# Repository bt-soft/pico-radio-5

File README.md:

# Pico-Radio-5

## Hardver részletesen

A Pico-Radio-5 egy fejlett, több sávos rádióvevő, amely a Raspberry Pi Pico (RP2040) mikrokontroller köré épül. A főbb hardverelemek:

- **Raspberry Pi Pico**  
  ARM Cortex-M0+ dual-core MCU, 2MB flash, 264kB RAM, USB programozás.
- **SI4735 rádió IC**  
  Digitális rádióvevő chip, amely támogatja az FM (RDS), AM (MW, LW, SW) sávokat, digitális vezérléssel (I2C).
- **TFT érintőkijelző**  
  320x240 vagy 480x320 felbontású, színes, érintésérzékeny kijelző (TFT_eSPI driverrel).
- **Rotary encoder**  
  Mechanikus forgó kódoló, amely a frekvencia, hangerő, menük vezérlésére szolgál (kattintás érzékelés is).
- **Hangkimenet**  
  3.5mm jack vagy beépített hangszóró, SI4735 audio kimenet közvetlenül vagy erősítőn keresztül.
- **Akkumulátor mérés**  
  Feszültségosztóval a Pico ADC-n keresztül, töltöttség kijelzés.
- **EEPROM**  
  Állomásmemória, beállítások tartós tárolása.
- **Egyéb**  
  Nyomógombok, szenzorok (pl. hőmérséklet), LED-ek, opcionális bővítések.

A részletes kapcsolási rajzok, NYÁK-tervek a `doc/` mappában találhatók:
- [Kapcsolási rajz (PDF)](doc/pico-radio-5-sch.pdf)
- [NYÁK terv (PDF)](doc/pico-radio-5-pcb.pdf)

## Szoftver részletesen

A szoftver PlatformIO környezetben, C++ nyelven, Arduino frameworkre épül. Főbb könyvtárak: PU2CLR SI4735, TFT_eSPI, RPI_PICO_TimerInterrupt.

### Fő funkciók

- **Rádió sávok**: FM (RDS), AM (MW, LW, SW), SSB/CW támogatás (ha SI4735 patch betöltve)
- **Állomáskeresés, finomhangolás**: automatikus és kézi keresés, lépésköz választás
- **Állomásmemória**: FM/AM/SW/LW sávonként, EEPROM-ban tárolva
- **RDS támogatás**: FM sávban állomásnév, rádiószöveg, PTY, óra
- **Grafikus kezelőfelület**: érintőképernyő, rotary encoder, menük, dialógusok, státuszsor
- **Képernyővédő**: animált frekvencia kijelzés, energiatakarékosság
- **Spektrumkijelzés**: FFT-alapú vizualizáció (ha támogatott)
- **Beállítások**: hangerő, sáv, lépésköz, kijelző fényerő, képernyővédő időzítés, stb.
- **Akkumulátor kijelzés**: töltöttség százalékban, színkódolva
- **Debug és diagnosztika**: soros porton részletes log, hibakereséshez

### Mappastruktúra

- `src/` – Fő forráskód (képernyők, rádió logika, UI, stb.)
- `include/` – Fejlécfájlok, interfészek, konstansok
- `doc/` – Dokumentáció, kapcsolási rajzok, NYÁK-tervek, minták
- `test/` – Egységtesztek, tesztkódok
- `platformio.ini` – PlatformIO projektkonfiguráció

### Főbb forrásfájlok

- `main.cpp` – Inicializálás, fő programciklus
- `ScreenFM.cpp`, `ScreenAM.cpp`, stb. – Különböző rádió sávok kezelői
- `ScreenSaverScreen.cpp` – Képernyővédő logika
- `FreqDisplay.cpp` – Frekvencia kijelző komponens
- `Config.cpp` – Beállítások kezelése, EEPROM mentés/betöltés
- `Si4735Manager.cpp` – SI4735 IC vezérlés, sávváltás, frekvenciaállítás

### Fordítás és feltöltés

1. Telepítsd a PlatformIO-t (ajánlott: VSCode bővítményként)
2. Nyisd meg a projektet VSCode-ban
3. Csatlakoztasd a Raspberry Pi Pico-t USB-n keresztül
4. Válaszd ki a Pico-t mint céleszközt
5. Kattints a Build (vagy Upload) gombra, vagy futtasd:  
   `pio run --target upload`
6. A feltöltés után a rádió automatikusan elindul

### Fejlesztői információk

- A kód moduláris, minden képernyő külön osztályban van
- A beállítások és állomásmemória EEPROM-ban tartósan tárolódik
- A hardveres I2C lábak, rotary encoder, kijelző, stb. pinjei a `pins.h`-ban konfigurálhatók
- Hibakereséshez a soros porton részletes log érhető el

## TFT_eSPI beállítás

A projekt a TFT_eSPI könyvtárat használja a kijelző kezeléséhez. A helyes működéshez a `doc/TFT_eSPI/User_Setup.h` fájlt be kell másolni a PlatformIO által használt TFT_eSPI könyvtár megfelelő mappájába. Ez általában:

```
.pio/libdeps/pico/TFT_eSPI/User_Setup.h
```

A másolás után a kijelző a projektben definiált beállításokkal fog működni. Ha másik kijelzőt használsz, módosítsd a `User_Setup.h`-t a saját hardveredhez.

## Licenc

A projekt szabadon felhasználható, módosítható, forrásmegjelöléssel. Lásd a forráskód fejléceit.

---

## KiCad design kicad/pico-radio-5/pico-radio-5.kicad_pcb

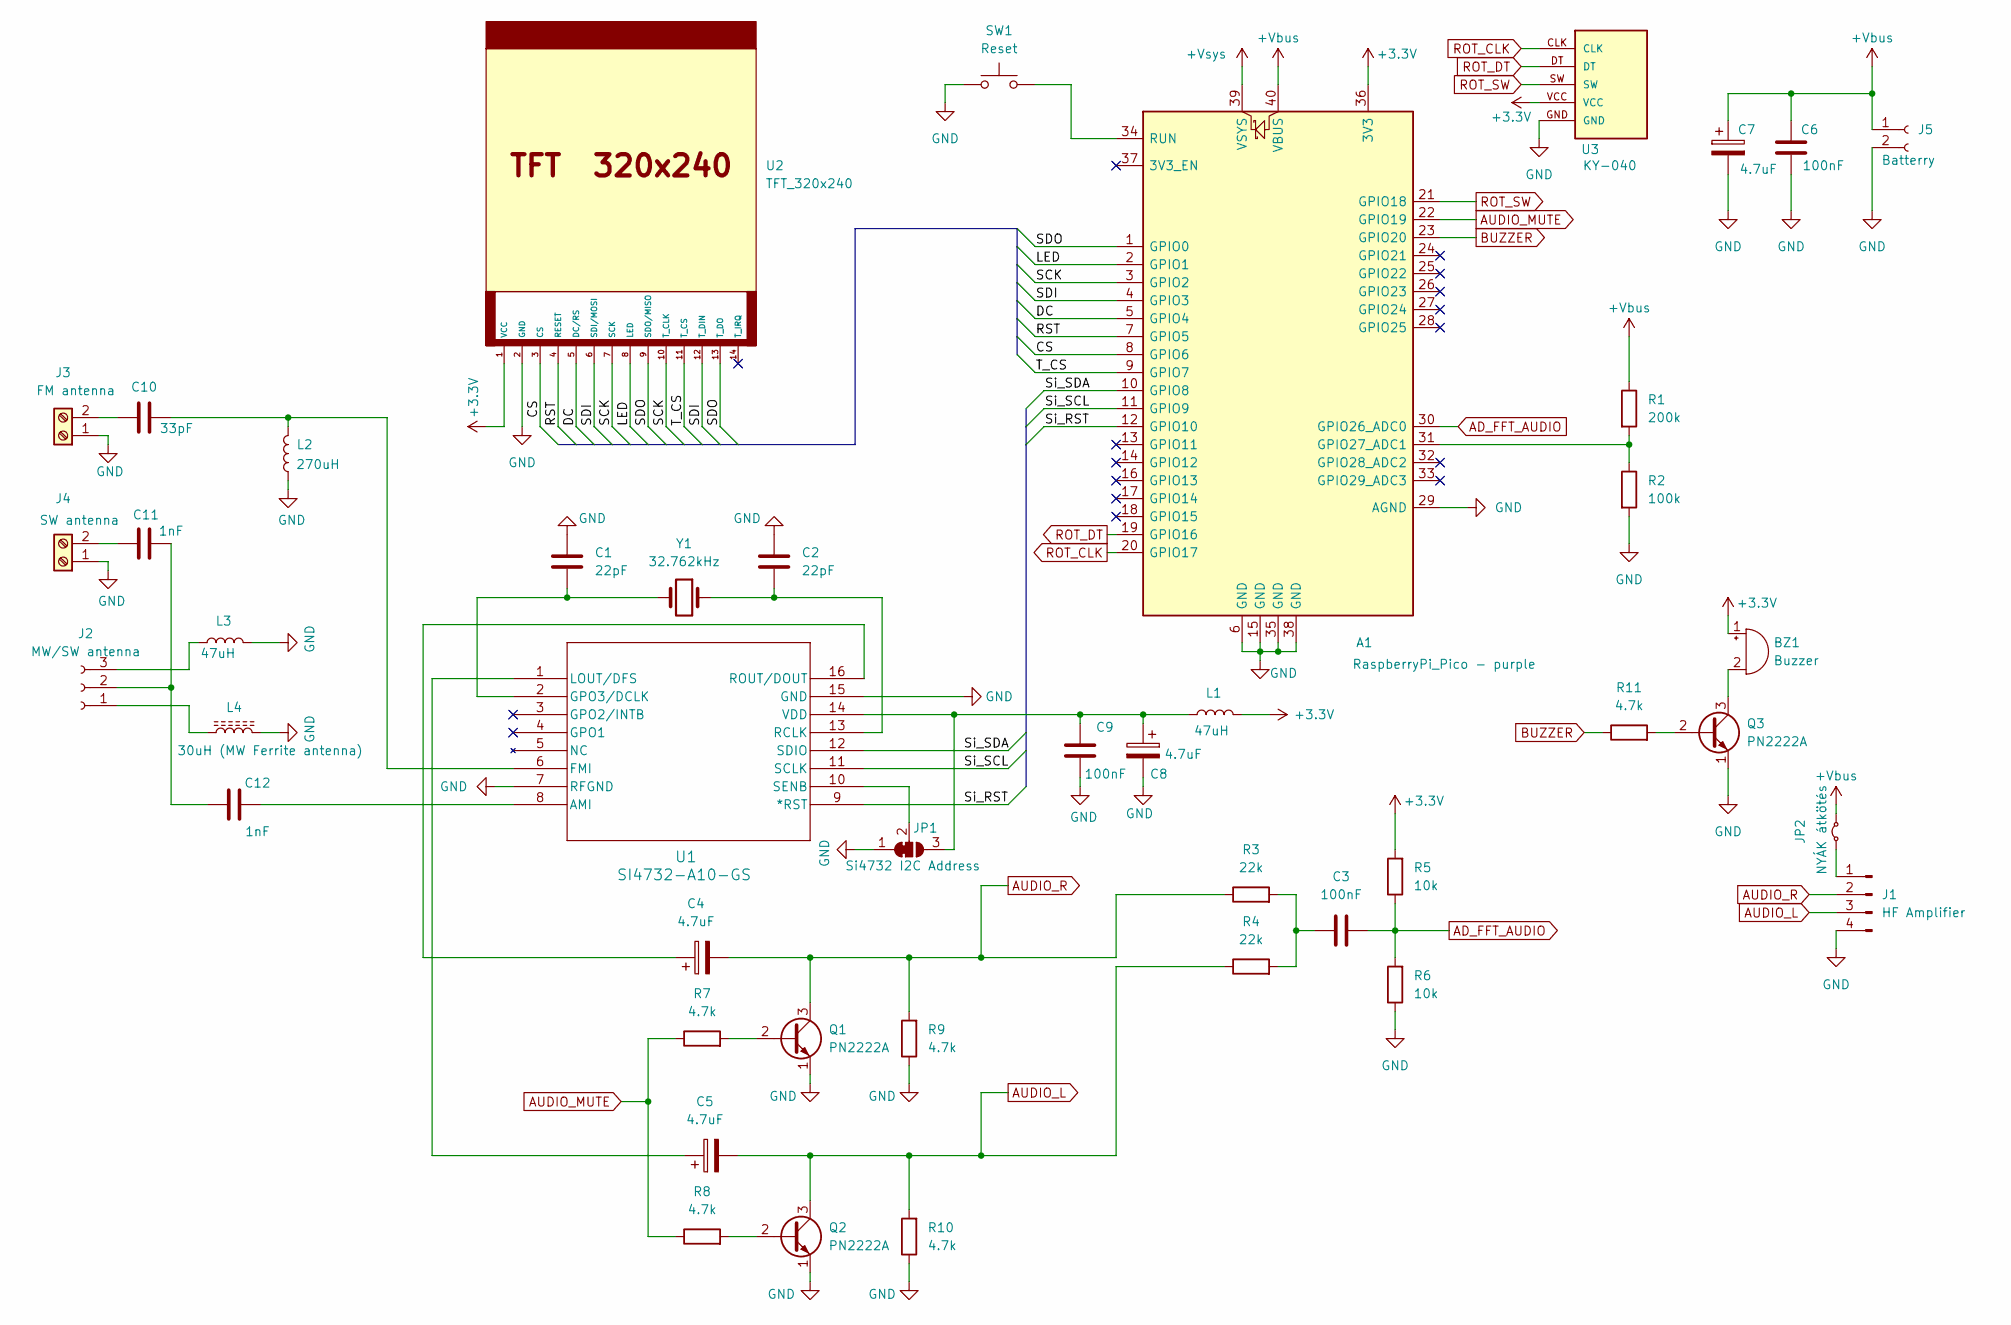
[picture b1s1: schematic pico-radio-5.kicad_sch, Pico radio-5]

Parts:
A1: RaspberryPi_Pico - purple; RaspberryPi_Pico_Common_THT-simple
BZ1: Buzzer; Buzzer_12x9.5RM7.6
C1, C2: 22pF; C_Disc_D3.0mm_W1.6mm_P2.50mm
C3, C6, C9: 100nF; C_Disc_D7.0mm_W2.5mm_P5.00mm
C4, C5, C7, C8: 4.7uF; CP_Radial_D5.0mm_P2.50mm
C10: 33pF; C_Disc_D3.0mm_W1.6mm_P2.50mm
C11, C12: 1nF; C_Disc_D3.0mm_W1.6mm_P2.50mm
J1: HF Amplifier; PinHeader_1x04_P2.54mm_Vertical
J2: MW/SW antenna; PinHeader_1x03_P2.54mm_Vertical
J3: FM antenna; TerminalBlock_4Ucon_1x02_P3.50mm_Horizontal
J4: SW antenna; TerminalBlock_4Ucon_1x02_P3.50mm_Horizontal
J5: Batterry; PinHeader_1x02_P2.54mm_Vertical
JP1: Si4732 I2C Address; SolderJumper-3_P1.3mm_Bridged12_RoundedPad1.0x1.5mm
JP2: NYÁK átkötés; R_Axial_DIN0207_L6.3mm_D2.5mm_P10.16mm_Horizontal
L1, L3: 47uH; R_Axial_DIN0207_L6.3mm_D2.5mm_P10.16mm_Horizontal
L2: 270uH; R_Axial_DIN0207_L6.3mm_D2.5mm_P10.16mm_Horizontal
L4: 30uH (MW Ferrite antenna); PinHeader_1x02_P2.54mm_Vertical
Q1, Q2, Q3: PN2222A; TO-92_Inline
R1: 200k; R_Axial_DIN0207_L6.3mm_D2.5mm_P10.16mm_Horizontal
R2: 100k; R_Axial_DIN0207_L6.3mm_D2.5mm_P10.16mm_Horizontal
R3, R4: 22k; R_Axial_DIN0207_L6.3mm_D2.5mm_P10.16mm_Horizontal
R5, R6: 10k; R_Axial_DIN0207_L6.3mm_D2.5mm_P10.16mm_Horizontal
R7, R8, R9, R10, R11: 4.7k; R_Axial_DIN0207_L6.3mm_D2.5mm_P10.16mm_Horizontal
SW1: Reset; PinHeader_1x02_P2.54mm_Vertical
U1: SI4732-A10-GS; SOIC_A10-GS_SIL
U2: TFT_320x240; PinHeader_1x14_P2.54mm_Vertical
U3: KY-040; KY-040-PORT
Y1: 32.762kHz; Crystal_C38-LF_D3.0mm_L8.0mm_Horizontal

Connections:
+3.3V: A1.36 (3V3), BZ1.1 (+), L1.2, R5.2, U2.1 (VCC), U3.VCC
+Vbus: A1.40 (VBUS), C6.1, C7.1, J5.1, JP2.2 (B), R1.1
+Vsys: A1.39 (VSYS)
/CS: A1.8 (GPIO6), U2.3 (CS)
/DC: A1.5 (GPIO4), U2.5 (DC/RS)
/LED: A1.2 (GPIO1), U2.8 (LED)
/RST: A1.7 (GPIO5), U2.4 (RESET)
/SCK: A1.3 (GPIO2), U2.7 (SCK), U2.10 (T_CLK)
/SDI: A1.4 (GPIO3), U2.6 (SDI/MOSI), U2.12 (T_DIN)
/SDO: A1.1 (GPIO0), U2.9 (SDO/MISO), U2.13 (T_DO)
/Si_RST: A1.12 (GPIO10), U1.9 (*RST)
/Si_SCL: A1.11 (GPIO9), U1.11 (SCLK)
/Si_SDA: A1.10 (GPIO8), U1.12 (SDIO)
/T_CS: A1.9 (GPIO7), U2.11 (T_CS)
AD_FFT_AUDIO: A1.30 (GPIO26_ADC0), C3.2, R5.1, R6.2
AUDIO_L: C5.2, J1.3, Q2.3 (C), R4.1, R10.2
AUDIO_MUTE: A1.22 (GPIO19), R7.1, R8.1
AUDIO_R: C4.2, J1.2, Q1.3 (C), R3.1, R9.2
BUZZER: A1.23 (GPIO20), R11.1
GND: A1.6 (GND), A1.15 (GND), A1.29 (AGND), A1.35 (GND), A1.38 (GND), C1.2, C2.1, C6.2, C7.2, C8.2, C9.1, J1.4, J3.1, J4.1, J5.2, JP1.1 (A), L2.1, L3.2, L4.2, Q1.1 (E), Q2.1 (E), Q3.1 (E), R2.2, R6.1, R9.1, R10.1, SW1.1, U1.7 (RFGND), U1.15 (GND), U2.2 (GND), U3.GND
unnamed: A1.31 (GPIO27_ADC1), R1.2, R2.1
unnamed: A1.34 (RUN), SW1.2
unnamed: BZ1.2 (-), Q3.3 (C)
unnamed: C3.1, R3.2, R4.2
unnamed: J1.1, JP2.1 (A)
unnamed: J2.1, L4.1
unnamed: C11.2, C12.2, J2.2
unnamed: J2.3, L3.1
unnamed: C10.2, J3.2
unnamed: C11.1, J4.2
unnamed: C8.1, C9.2, JP1.3 (B), L1.1, U1.14 (VDD)
unnamed: JP1.2 (C), U1.10 (SENB)
unnamed: Q1.2 (B), R7.2
unnamed: Q2.2 (B), R8.2
unnamed: Q3.2 (B), R11.2
unnamed: C12.1, U1.8 (AMI)
unnamed: C10.1, L2.2, U1.6 (FMI)
unnamed: C1.1, U1.2 (GPO3/DCLK), Y1.2
unnamed: C5.1, U1.1 (LOUT/DFS)
unnamed: C2.2, U1.13 (RCLK), Y1.1
unnamed: C4.1, U1.16 (ROUT/DOUT)
ROT_CLK: A1.20 (GPIO17), U3.CLK
ROT_DT: A1.19 (GPIO16), U3.DT
ROT_SW: A1.21 (GPIO18), U3.SW

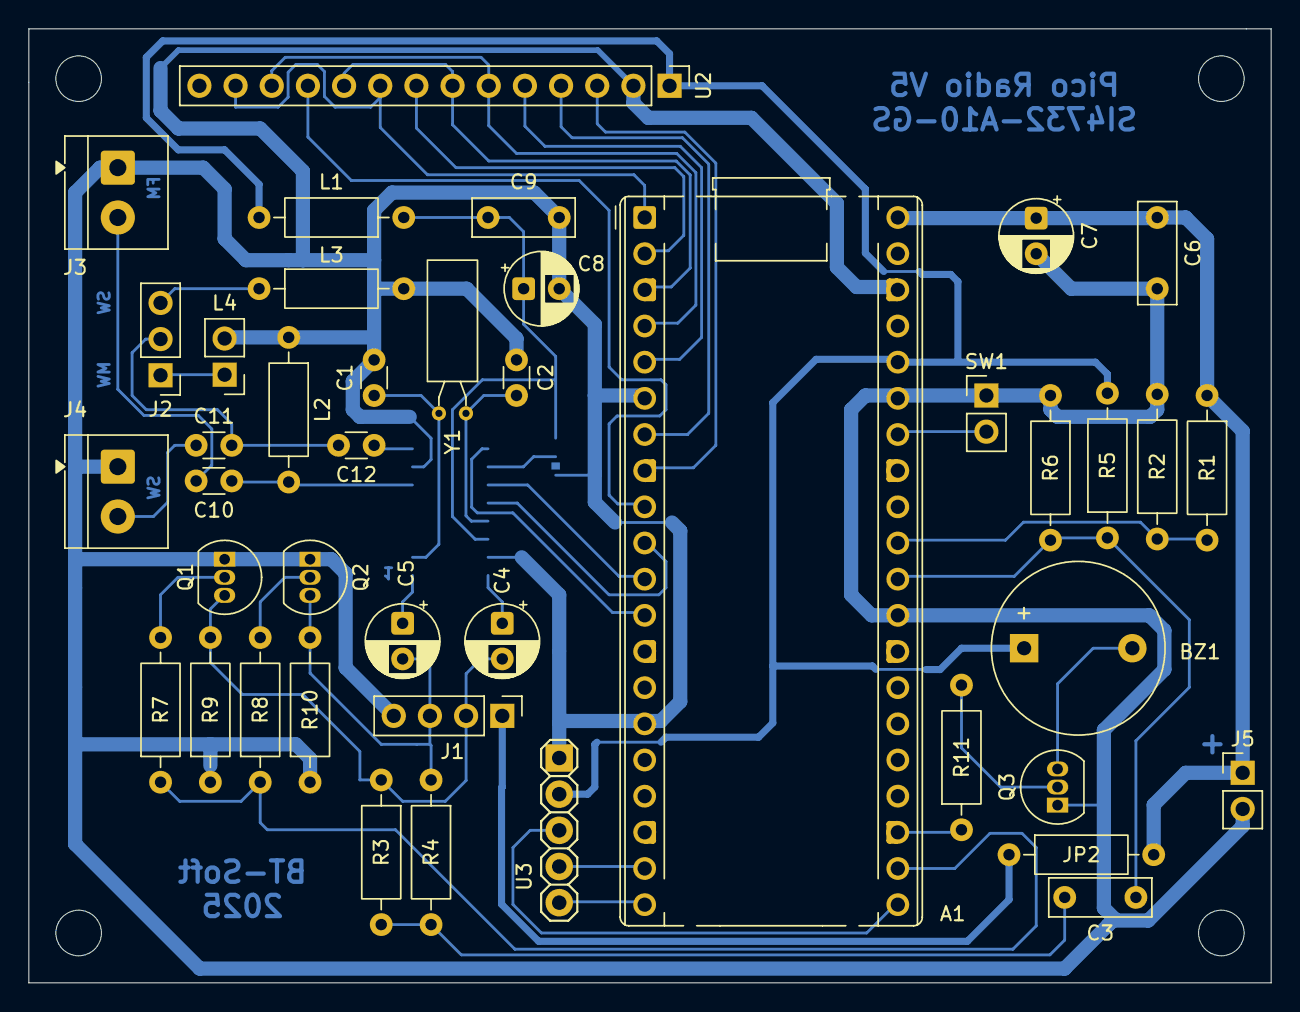
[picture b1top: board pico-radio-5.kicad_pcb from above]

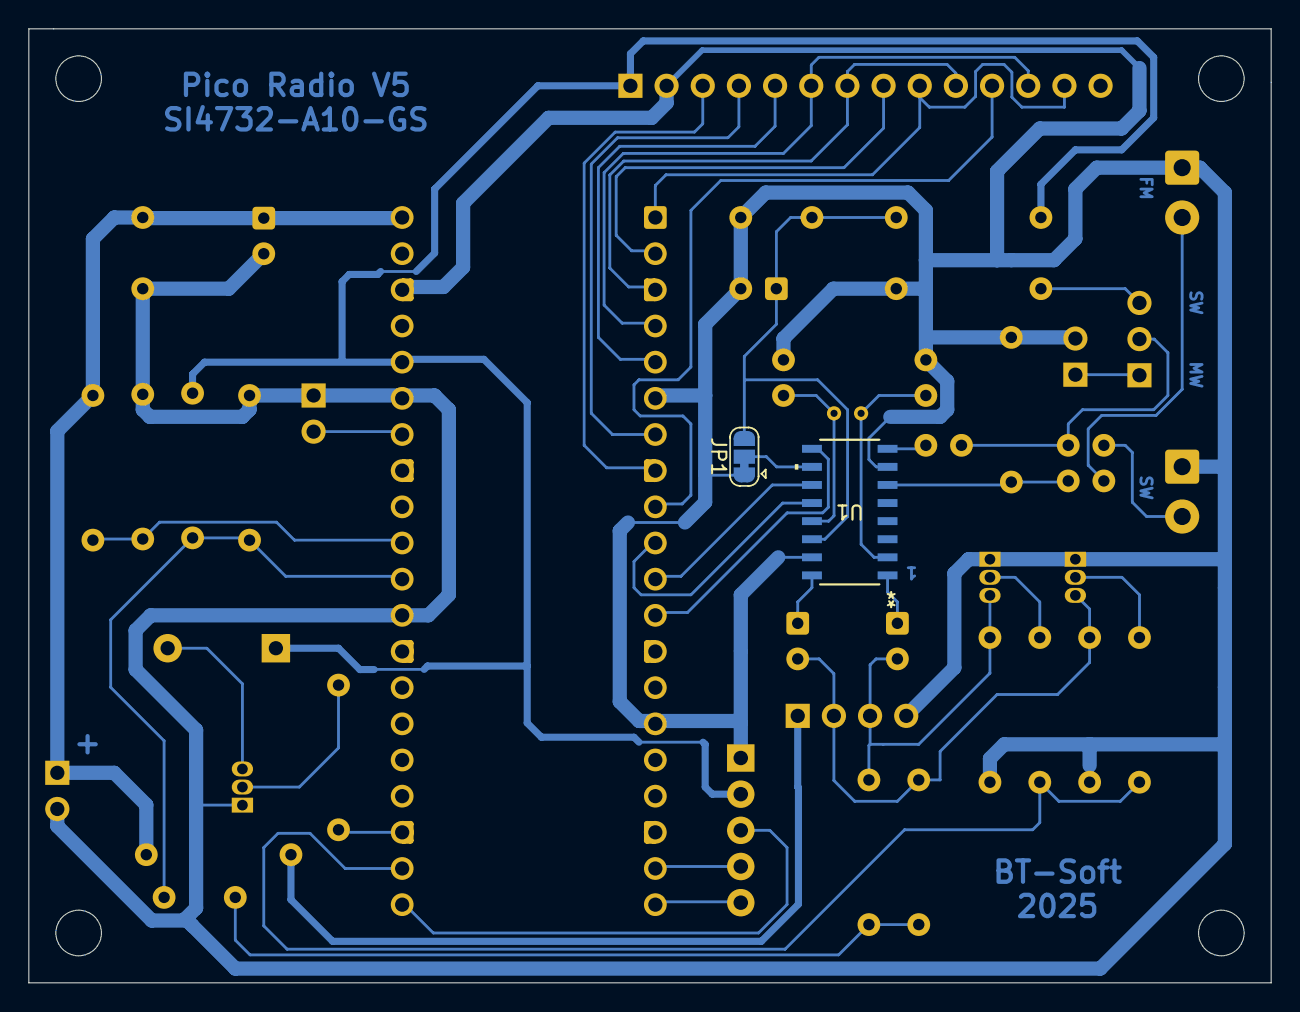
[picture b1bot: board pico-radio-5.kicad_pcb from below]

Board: 2 copper layers, 87.2 x 67.0 mm, 44 parts (2 on the bottom side), 43 nets.

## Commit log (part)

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2025-06-29 Add rtVars and utils implementations for radio control features
    - Implemented rtVars.cpp to manage radio variables including mute status, frequency display, BFO states, and squelch settings.
    - Created utils.cpp for utility functions such as serial wait, TFT calibration, error display, beeping functions, string manipulation, and CRC16 calculation.
    - Added necessary includes and namespace organization for better code structure and readability.
2025-06-29 Implement Screen Memory Management and Virtual Keyboard Dialog
    - Added ScreenMemory class for managing FM/AM station memory, including functionalities for adding, editing, and deleting stations.
    - Implemented UI components for displaying station lists and horizontal button navigation.
    - Integrated station loading and refreshing mechanisms to keep the UI updated with current station data.
    - Developed StereoIndicator class to visually indicate stereo/mono status.
    - Created VirtualKeyboardDialog for user input with a customizable on-screen keyboard, including special keys for backspace and clear.
    - Enhanced user experience with dynamic button states and cursor visibility in the virtual keyboard
2025-06-29 Initialize rdsStationName in ScreenMemory constructor and update setParameters for String conversion
2025-06-29 Implement ScreenAM class for AM radio functionality with specific button handling and UI management
2025-06-29 Refactor ScreenAM: improve code readability by adding whitespace and updating comments for clarity
2025-06-29 Update defines.h: comment out DEBUG_WAIT_FOR_SERIAL definition and adjust ScreenAM layout for S-Meter component
2025-07-07 Update processBandButton: add dialog title for band selection
2025-07-07 Add Audio Display and Analyzer Components
    - Implemented AudioDisplayComponent for visualizing audio data with various modes (spectrum, oscilloscope, waterfall).
    - Created AudioAnalyzer for processing audio input and performing FFT calculations.
    - Added support for CW/RTTY tuning and peak hold functionality.
    - Integrated touch handling for mode switching in the display component.
    - Established a global configuration reference for managing settings.
    - Enhanced debugging output for better traceability during audio processing.
2025-07-08 Add AudioProcessor class for audio processing and visualization
2025-07-08 Refactor AudioProcessor: consolidate visualization data into a single union structure, optimizing memory usage and simplifying API interactions for different visualization modes
2025-07-09 Add DC offset calibration to AudioProcessor and remove unused comments from ScreenFM
2025-07-09 Add forced redraw functionality and optimize rendering with sprite usage in SpectrumVisualizationComponent
2025-07-09 Add audio processing and visualization components
    - Implemented AudioProcessor class for audio data handling, FFT calculations, and various visualization modes (spectrum, oscilloscope, envelope, waterfall).
    - Created SharedAudioData structure for inter-core communication and synchronization.
    - Added SimpleSpectrumDisplay class for displaying spectrum data.
    - Developed test files for audio processing and spectrum display functionalities.
    - Included necessary headers and defined constants for audio processing.
    - Established mutex locks for thread safety during data access.
2025-07-10 Remove obsolete AudioProcessor header and implementation files
2025-07-10 Update iScreenManager to use double pointer for improved screen management
2025-07-10 Refactor: Remove AudioProcessor initialization from setup
    - Removed the inclusion of the AudioProcessor header and its initialization from the setup function.
    - This change simplifies the setup process by eliminating unnecessary delays and dependencies related to Core1 audio processing.
2025-07-10 Refactor: Adjust sample decimation factor and improve rendering flags for frequency labels
2025-07-11 Refactor: Adjust spectrum component bounds and simplify touch event handling
2025-07-11 Refactor: Comment out audio FFT gain in configuration and clean up audio mode settings
2025-07-11 Refactor: Remove unused force redraw method and simplify border drawing logic in SpectrumVisualizationComponent
2025-07-11 Change FFT resolution settings
2025-07-11 Refactor: Rename FFT configuration methods and update related settings in ScreenSetupAudioProc
2025-07-11 Fix: Update data availability checks in SpectrumVisualizationComponent to prevent flickering and ensure proper rendering
2025-07-11 Enhance: Implement frame-based adaptive gain system in SpectrumVisualizationComponent
2025-07-11 Enhance: Set font and text size for muted message display in SpectrumVisualizationComponent
2025-07-12 Enhance: Update program name and version to Pico Radio v5
2025-07-12 Enhance: Implement advanced CW/RTTY decoder with state management and character processing
2025-07-13 Refactor AudioProcessor and related components for improved FFT handling and noise reduction
    - Introduced setSamplingFrequency method in AudioProcessor for dynamic sampling frequency adjustment.
    - Added NOISE_REDUCTION_ANALOG_SAMPLES_COUNT constant for better readability in noise reduction logic.
    - Updated FFT gain configuration references from miniAudioFftConfig to audioFftConfig in Config, DebugDataInspector, ScreenSetupAudioProc, and SpectrumVisualizationComponent.
    - Enhanced debug messages for clarity and consistency in SpectrumVisualizationComponent.
    - Removed unused methods and improved code structure for better maintainability.
    - Ensured thread-safe retrieval of FFT size and bin width
2025-07-13 Enhance: Add updateMaxDisplayFrequencyHz method to SpectrumVisualizationComponent and integrate it with AudioCore1Manager for dynamic frequency updates
2025-07-13 Enhance: Improve audio processing pause handling with mutex protection during EEPROM operations
2025-07-14 Enhance: Fix bandwidth index assignment logic for AM and FM demodulation types in handleAfBWButton
2025-07-14 Enhance: Update tuning aid frequency range logic for CW and RTTY modes in SpectrumVisualizationComponent
2025-07-14 Enhance: Optimize oscilloscope rendering logic to reduce flickering by conditionally clearing the sprite only when new data is available
2025-07-15 Enhance: Refactor FFT sampling frequency assignment and streamline bandwidth label handling in ScreenRadioBase
2025-07-15 Enhance: Adjust indicator drawing area for improved visibility in SpectrumVisualizationComponent
2025-07-15 Enhance: Add frequency label rendering and improve mode indicator visibility in SpectrumVisualizationComponent
2025-07-15 Enhance: Implement frequency formatting utility and integrate it into SpectrumVisualizationComponent for improved label rendering
2025-07-15 Enhance: Adjust envelope input gain for improved amplitude scaling in SpectrumVisualizationComponent
2025-07-15 Refactor CwGoertzelDecoder and SpectrumVisualizationComponent
    - Updated CwGoertzelDecoder to include current time in processBlock method for improved timing accuracy.
    - Enhanced internal state management in CwGoertzelDecoder with additional variables for Morse code decoding.
    - Modified SpectrumVisualizationComponent constructor to initialize decoderManager and set CW parameters.
    - Adjusted frame rate for spectrum visualization to 20 FPS for better performance.
    - Consolidated rendering functions for CW and RTTY waterfalls into a single method.
    - Added helper functions for mode and frequency label rendering to improve code clarity and maintainability.
2025-07-17 Enhance: Implement timer interrupt handling and initialization for AudioCore1Manager
2025-07-17 Enhance: Update oscilloscope data handling in AudioCore1Manager and AudioProcessor, including sample count management
2025-07-17 Enhance: Refactor SplashScreen usage in setup for better memory management
2025-07-17 Enhance: Refactor AudioCore1Manager to improve pause handling and remove unused timer functionality
2025-07-17 Enhance: Refactor audio processing to use float types for FFT and spectrum data handling
2025-07-18 Enhance: Restore preferred demodulation mode when switching bands in processBandButton
2025-07-18 Enhance: Implement CW/RTTY decoder and integrate with spectrum visualization
2025-07-18 Enhance: Refactor CW decoder to implement adaptive timing and dynamic thresholding for improved signal detection
2025-07-18 Enhance: Refactor processFftData to improve CW element handling and adapt logic from pico-radio-2
2025-07-19 Refactor CW Decoder: Replace CwRttyDecoder with CwDecoder
    - Updated ScreenAM to include CwDecoder instead of CwRttyDecoder.
    - Removed CwRttyDecoder implementation and header files.
    - Introduced CwDecoder class with enhanced functionality for Morse code decoding.
    - Implemented adaptive thresholding and noise level calculations in CwDecoder.
    - Added state machine logic for handling Morse code timing and decoding.
    - Updated relevant includes and object instantiations in ScreenAM.
2025-07-19 Refactor: Remove unused Morse table initialization and clean up CwDecoder methods for improved clarity
2025-07-19 Enhance: Update detectTone method to return tone detection result for improved functionality
2025-07-19 Enhance: Increase optimal FFT size for CW mode to improve signal detection accuracy
2025-08-04 Enhance audio processing by implementing noise thresholding and improving gain factor handling
2025-08-09 Add lock file for pico-radio-5 schematic to prevent concurrent edits
2025-08-10 pictures
2025-08-10 Implement code changes to enhance functionality and improve performance
2025-08-10 Update device photo in README.md for accuracy
2025-08-29 Remove outdated backup ZIP files from pico-radio project
2025-09-02 Fix EEPROM size definition and update memory info calculations in SystemInfoDialog
2025-09-18 Refactor RDS data timeout handling to prevent cache clearing on timeout; only clear on explicit data loss or station change
2025-09-18 Fix indentation for implementation comments in UIButton, UIColorPalette, MessageDialog, and Si4735Band
2025-09-18 Add beeper feedback on button press and touch events when enabled
2025-09-19 Refactor debug logging in AudioCore1Manager and clarify method call in ScreenAM
2025-09-26 Enhance CwDecoder with adaptive timing features and improve Morse code handling
2025-09-26 Reduce maximum character limit for scrolling text to 80 for testing; add debug logging for text length and scrolling actions
2025-09-27 Refactor CwDecoder: adjust search window size for tone detection and improve debug logging for detected tones
2025-09-27 Refactor renderSnrCurve: simplify tuning aid type setting and enhance frequency label rendering with background for better visibility
2025-09-27 Refactor SpectrumVisualizationComponent: enhance tuning aid type handling and improve SNR curve rendering with better text visibility
2025-09-27 Refactor RTTY decoder: enhance adaptive threshold logic with mark/space differentiation and improve SNR calculation for better signal detection
2025-09-27 Enhance RTTY decoder: improve handling of invalid stop bits and add debug logging for bit timing analysis
2025-09-27 Enhance RTTY decoder: add signal presence validation and tracking, improve SNR thresholds, and adjust default baud rate to 75
2025-09-28 Add optimal sampling frequency handling for CW/RTTY modes and update tuning aid calculations based on current HF bandwidth
2025-09-28 Update default CW and RTTY frequencies for improved compatibility; adjust adaptive SNR threshold and sensitivity constants for better weak signal detection
2025-09-28 Enhance CwDecoder with detailed documentation and improve timing calibration logic
    - Added comprehensive comments and documentation for methods and parameters in CwDecoder.
    - Improved the timing calibration logic for better handling of Morse code signals.
    - Enhanced debug output for clarity and consistency.
    - Refined adaptive threshold adjustments based on signal detection.
2025-09-28 Remove debug log for long press detection in UITextBox loop method
2025-09-28 Update SNR threshold and clean up debug logs in CwDecoder and RttyDecoder
2025-09-28 Add debug logging for max display frequency in SpectrumVisualizationComponent and clean up constructor and destructor in ScreenAM and ScreenRadioBase
2025-10-04 Fix typos in configuration variables and update related references for consistency
